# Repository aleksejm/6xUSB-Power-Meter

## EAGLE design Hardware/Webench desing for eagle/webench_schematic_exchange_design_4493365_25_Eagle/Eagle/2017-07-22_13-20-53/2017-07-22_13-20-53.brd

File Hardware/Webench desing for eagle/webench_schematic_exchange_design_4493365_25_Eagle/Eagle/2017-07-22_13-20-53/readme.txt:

**********************************************************
*************  Important Instructions Follow  ************
**********************************************************
 
All files exported to: Z:\\44\\93\\4493365\\25\Eagle\2017-07-22_13-20-53\2017-07-22_13-20-53.xml

**********************************************************
*****************Schematic Instructions  *******************
**********************************************************

To import your new Schematic file into Eagle:

1. Unzip the downloaded folder files to local directory and Start Eagle.
2. Select "File"->"Open"->"Schematic..." from the menu at the top of
the screen.
3. Browse to your newly exported file and select the ".sch" file extension.
4. You should now see your schamtic available in Eagle.

**********************************************************
*******************  PCB Instructions  *******************
**********************************************************

To import your new BOARD file into Eagle:

1. Unzip the downloaded folder files to local directory and Start Eagle.
2. Select "File"->"Open"->"Board..." from the menu at the top of
the screen.
3. Browse to your newly exported file and select the ".brd" file extension.
4. Planes will need to be repoured to update the polygon fills
	1. Once your board is loaded, type "ratsnest" into the command
	   line and press the Enter key.
	2. The polygons should all be filled now.
5. You should now have an image of your board available in Eagle.

**********************************************************
*******************  LIB Instructions  *******************
**********************************************************

To import your new library into Eagle:

1. Start Eagle.
2. Select "File"->"New"->"Library" from the menu.
3. In the blank library window, select "File" -> "Execute Script"
from the menu.
5. Browse to your newly exported Eagle Script file (".scr" file extension)
6. After opening the file, the script will populate the new library.
Layer 93 should NOT exist.
7. Use "File"->Save As: "AcceleratedDesigns_Lib.lbr" and to the desired
location in Eagle native format.
8. Update schematic with the imported library, Select Library and click on Update; open the library file
	and sync. each part.

For additional information, please visit this site:
http://www.accelerated-designs.com/help/Eagle_import.html

You may also find this video helpful:
http://youtu.be/5jGuWY-Yy3Q

**********************************************************
**********************************************************
**********************************************************

Component "C0805C102K5RACTU" renamed to "C0805C102K5RACTU"
Component "EMK212B7474KD-T" renamed to "EMK212B7474KD-T"
Component "08053C104KAT2A" renamed to "08053C104KAT2A"
Component "WB_CURRENT_LOAD" renamed to "WB_CURRENT_LOAD"
Component "6SVPC330M" renamed to "6SVPC330M"
Component "CC0805KRX7R9BB153" renamed to "CC0805KRX7R9BB153"
Component "EMK212B7105KG-T" renamed to "EMK212B7105KG-T"
Component "WB_GND" renamed to "WB_GND"
Component "XAL1010-472MEB" renamed to "XAL1010-472MEB"
Component "CSD16321Q5" renamed to "CSD16321Q5"
Component "CSD18509Q5B" renamed to "CSD18509Q5B"
Component "ERJ-6ENF1002V" renamed to "ERJ-6ENF1002V"
Component "ERJ-6ENF7322V" renamed to "ERJ-6ENF7322V"
Component "CRCW0805464RFKEA" renamed to "CRCW0805464RFKEA"
Component "ERJ-6ENF2373V" renamed to "ERJ-6ENF2373V"
Component "LM3150MH/NOPB" renamed to "LM3150MH/NOPB"
Component "WB_BATTERY" renamed to "WB_BATTERY"
Component "C3216X5R1E476M160AC" renamed to "C3216X5R1E476M160AC"
The Symbol WB_CONTINUATION was missing a RefDes attribute, a refdes was created for the symbol.
The Symbol WB_CONTINUATION was missing a Type attribute, a type was created for the symbol.
The Symbol WB_CONTINUATION was missing a Value attribute, a value was created for the symbol.
The Symbol WB_CFF_BLOCK was missing a RefDes attribute, a refdes was created for the symbol.
The Symbol WB_CFF_BLOCK was missing a Type attribute, a type was created for the symbol.
The Symbol WB_CFF_BLOCK was missing a Value attribute, a value was created for the symbol.
The Symbol WB_BLOCK_IO was missing a RefDes attribute, a refdes was created for the symbol.
The Symbol WB_BLOCK_IO was missing a Type attribute, a type was created for the symbol.
The Symbol WB_BLOCK_IO was missing a Value attribute, a value was created for the symbol.
The Symbol WB_CURRENT_PROBE was missing a RefDes attribute, a refdes was created for the symbol.
The Symbol WB_CURRENT_PROBE was missing a Type attribute, a type was created for the symbol.
The Symbol WB_CURRENT_PROBE was missing a Value attribute, a value was created for the symbol.
The Symbol WB_N_MOSFET was missing a RefDes attribute, a refdes was created for the symbol.
The Symbol WB_N_MOSFET was missing a Type attribute, a type was created for the symbol.
The Symbol WB_N_MOSFET was missing a Value attribute, a value was created for the symbol.
The Symbol WB_LM3150 was missing a RefDes attribute, a refdes was created for the symbol.
The Symbol WB_LM3150 was missing a Type attribute, a type was created for the symbol.
The Symbol WB_LM3150 was missing a Value attribute, a value was created for the symbol.
The Symbol WB_VOLTAGE_PROBE was missing a RefDes attribute, a refdes was created for the symbol.
The Symbol WB_VOLTAGE_PROBE was missing a Type attribute, a type was created for the symbol.
The Symbol WB_VOLTAGE_PROBE was missing a Value attribute, a value was created for the symbol.
The Symbol WB_PWL_VOLTAGE_SOURCE was missing a RefDes attribute, a refdes was created for the symbol.
The Symbol WB_PWL_VOLTAGE_SOURCE was missing a Type attribute, a type was created for the symbol.
The Symbol WB_PWL_VOLTAGE_SOURCE was missing a Value attribute, a value was created for the symbol.
The Symbol WB_SOURCE_RESISTOR was missing a RefDes attribute, a refdes was created for the symbol.
The Symbol WB_SOURCE_RESISTOR was missing a Type attribute, a type was created for the symbol.
The Symbol WB_SOURCE_RESISTOR was missing a Value attribute, a value was created for the symbol.
The Symbol WB_PRIM_PWL_VOLTAGE_SOURCE was missing a RefDes attribute, a refdes was created for the symbol.
The Symbol WB_PRIM_PWL_VOLTAGE_SOURCE was missing a Type attribute, a type was created for the symbol.
The Symbol WB_PRIM_PWL_VOLTAGE_SOURCE was missing a Value attribute, a value was created for the symbol.
The Symbol WB_PRIM_STARTUP_VOLTAGE_SOURCE was missing a RefDes attribute, a refdes was created for the symbol.
The Symbol WB_PRIM_STARTUP_VOLTAGE_SOURCE was missing a Type attribute, a type was created for the symbol.
The Symbol WB_PRIM_STARTUP_VOLTAGE_SOURCE was missing a Value attribute, a value was created for the symbol.
The Symbol WB_STARTUP_VOLTAGE_SOURCE was missing a RefDes attribute, a refdes was created for the symbol.
The Symbol WB_STARTUP_VOLTAGE_SOURCE was missing a Type attribute, a type was created for the symbol.
The Symbol WB_STARTUP_VOLTAGE_SOURCE was missing a Value attribute, a value was created for the symbol.
The Symbol WB_PRIMITIVE_BATTERY was missing a RefDes attribute, a refdes was created for the symbol.
The Symbol WB_PRIMITIVE_BATTERY was missing a Type attribute, a type was created for the symbol.
The Symbol WB_PRIMITIVE_BATTERY was missing a Value attribute, a value was created for the symbol.
The Symbol WB_PWL_CURRENT_LOAD was missing a RefDes attribute, a refdes was created for the symbol.
The Symbol WB_PWL_CURRENT_LOAD was missing a Type attribute, a type was created for the symbol.
The Symbol WB_PWL_CURRENT_LOAD was missing a Value attribute, a value was created for the symbol.
The Symbol WB_LOAD_RESISTOR was missing a RefDes attribute, a refdes was created for the symbol.
The Symbol WB_LOAD_RESISTOR was missing a Type attribute, a type was created for the symbol.
The Symbol WB_LOAD_RESISTOR was missing a Value attribute, a value was created for the symbol.

Ultra Librarian Gold 8.1.204 Process Report

Message - Padstack "RX44Y57D0T" Shape(4) is a CIRCLE with no diameter.
Message - Padstack "RX44Y71D0T" Shape(4) is a CIRCLE with no diameter.
Message - Padstack "RX128Y31D0T" Shape(4) is a CIRCLE with no diameter.
Message - Padstack "RX94Y445D0T" Shape(4) is a CIRCLE with no diameter.
Message - Padstack "RX31p5Y27p56D0T" Shape(4) is a CIRCLE with no diameter.
Message - Padstack "RX4p3Y4p56D0T" Shape(4) is a CIRCLE with no diameter.
Message - Padstack "RX1p37Yp71D0T" Shape(4) is a CIRCLE with no diameter.
Message - Padstack "RX3p85Y4p52D0T" Shape(4) is a CIRCLE with no diameter.
Message - Padstack "RX56Y14D0T" Shape(4) is a CIRCLE with no diameter.
Message - Padstack "RX118Y122D0T" Shape(4) is a CIRCLE with no diameter.
Message - Symbol "WB_CAPACITOR" has as multiple attributes named "TYPE".
One of the attributes was renamed to "TYPE_2".
Message - Component "C0805C102K5RACTU" attribute "Cap" references text style "" that is not in the database.
The default pattern text style "H50s3" was substituted.
Message - Component "C0805C102K5RACTU" attribute "ESR" references text style "" that is not in the database.
The default pattern text style "H50s3" was substituted.
Message - Component "C0805C102K5RACTU" attribute "IRMS" references text style "" that is not in the database.
The default pattern text style "H50s3" was substituted.
Message - Component "C0805C102K5RACTU" attribute "VDC" references text style "" that is not in the database.
The default pattern text style "H50s3" was substituted.
Message - Component "EMK212B7474KD-T" attribute "Cap" references text style "" that is not in the database.
The default pattern text style "H50s3" was substituted.
Message - Component "EMK212B7474KD-T" attribute "ESR" references text style "" that is not in the database.
The default pattern text style "H50s3" was substituted.
Message - Component "EMK212B7474KD-T" attribute "IRMS" references text style "" that is not in the database.
The default pattern text style "H50s3" was substituted.
Message - Component "EMK212B7474KD-T" attribute "VDC" references text style "" that is not in the database.
The default pattern text style "H50s3" was substituted.
Message - Component "08053C104KAT2A" attribute "Cap" references text style "" that is not in the database.
The default pattern text style "H50s3" was substituted.
Message - Component "08053C104KAT2A" attribute "ESR" references text style "" that is not in the database.
The default pattern text style "H50s3" was substituted.
Message - Component "08053C104KAT2A" attribute "IRMS" references text style "" that is not in the database.
The default pattern text style "H50s3" was substituted.
Message - Component "08053C104KAT2A" attribute "VDC" references text style "" that is not in the database.
The default pattern text style "H50s3" was substituted.
Message - Component "6SVPC330M" attribute "Datasheet URL" references text style "" that is not in the database.
The default pattern text style "H50s3" was substituted.
Message - Component "6SVPC330M" attribute "Cap" references text style "" that is not in the database.
The default pattern text style "H50s3" was substituted.
Message - Component "6SVPC330M" attribute "ESR" references text style "" that is not in the database.
The default pattern text style "H50s3" was substituted.
Message - Component "6SVPC330M" attribute "IRMS" references text style "" that is not in the database.
The default pattern text style "H50s3" was substituted.
Message - Component "6SVPC330M" attribute "VDC" references text style "" that is not in the database.
The default pattern text style "H50s3" was substituted.
Message - Component "CC0805KRX7R9BB153" attribute "Cap" references text style "" that is not in the database.
The default pattern text style "H50s3" was substituted.
Message - Component "CC0805KRX7R9BB153" attribute "ESR" references text style "" that is not in the database.
The default pattern text style "H50s3" was substituted.
Message - Component "CC0805KRX7R9BB153" attribute "IRMS" references text style "" that is not in the database.
The default pattern text style "H50s3" was substituted.
Message - Component "CC0805KRX7R9BB153" attribute "VDC" references text style "" that is not in the database.
The default pattern text style "H50s3" was substituted.
Message - Component "EMK212B7105KG-T" attribute "Cap" references text style "" that is not in the database.
The default pattern text style "H50s3" was substituted.
Message - Component "EMK212B7105KG-T" attribute "ESR" references text style "" that is not in the database.
The default pattern text style "H50s3" was substituted.
Message - Component "EMK212B7105KG-T" attribute "IRMS" references text style "" that is not in the database.
The default pattern text style "H50s3" was substituted.
Message - Component "EMK212B7105KG-T" attribute "VDC" references text style "" that is not in the database.
The default pattern text style "H50s3" was substituted.
Message - Component "XAL1010-472MEB" attribute "L" references text style "" that is not in the database.
The default pattern text style "H50s3" was substituted.
Message - Component "XAL1010-472MEB" attribute "DCR" references text style "" that is not in the database.
The default pattern text style "H50s3" was substituted.
Message - Component "XAL1010-472MEB" attribute "IDC" references text style "" that is not in the database.
The default pattern text style "H50s3" was substituted.
Message - Component "ERJ-6ENF1002V" attribute "Resistance" references text style "" that is not in the database.
The default pattern text style "H50s3" was substituted.
Message - Component "ERJ-6ENF1002V" attribute "Power" references text style "" that is not in the database.
The default pattern text style "H50s3" was substituted.
Message - Component "ERJ-6ENF1002V" attribute "Tolerance" references text style "" that is not in the database.
The default pattern text style "H50s3" was substituted.
Message - Component "ERJ-6ENF7322V" attribute "Resistance" references text style "" that is not in the database.
The default pattern text style "H50s3" was substituted.
Message - Component "ERJ-6ENF7322V" attribute "Power" references text style "" that is not in the database.
The default pattern text style "H50s3" was substituted.
Message - Component "ERJ-6ENF7322V" attribute "Tolerance" references text style "" that is not in the database.
The default pattern text style "H50s3" was substituted.
Message - Component "CRCW0805464RFKEA" attribute "Resistance" references text style "" that is not in the database.
The default pattern text style "H50s3" was substituted.
Message - Component "CRCW0805464RFKEA" attribute "Power" references text style "" that is not in the database.
The default pattern text style "H50s3" was substituted.
Message - Component "CRCW0805464RFKEA" attribute "Tolerance" references text style "" that is not in the database.
The default pattern text style "H50s3" was substituted.
Message - Component "ERJ-6ENF2373V" attribute "Resistance" references text style "" that is not in the database.
The default pattern text style "H50s3" was substituted.
Message - Component "ERJ-6ENF2373V" attribute "Power" references text style "" that is not in the database.
The default pattern text style "H50s3" was substituted.
Message - Component "ERJ-6ENF2373V" attribute "Tolerance" references text style "" that is not in the database.
The default pattern text style "H50s3" was substituted.
Message - Component "LM3150MH/NOPB" attribute "Datasheet URL" references text style "" that is not in the database.
The default pattern text style "H50s3" was substituted.
Message - Component "LM3150MH/NOPB" attribute "Frequency" references text style "" that is not in the database.
The default pattern text style "H50s3" was substituted.
Message - Component "LM3150MH/NOPB" attribute "Imax" references text style "" that is not in the database.
The default pattern text style "H50s3" was substituted.
Message - Component "LM3150MH/NOPB" attribute "Package" references text style "" that is not in the database.
The default pattern text style "H50s3" was substituted.
Message - Component "LM3150MH/NOPB" attribute "Mktg_Package" references text style "" that is not in the database.
The default pattern text style "H50s3" was substituted.
Message - Component "LM3150MH/NOPB" attribute "NSID" references text style "" that is not in the database.
The default pattern text style "H50s3" was substituted.

TextStyle count:  24
Padstack count:   10
Pattern count:    7
Symbol count:     25
Component count:  18

Export

Component "C3216X5R1E476M160AC" has the following missing dependency and will be skipped: Footprint "1206L"
Footprint "WB_CURRENT_LOAD" has no layer data mapped and will be skipped.
Component "WB_CURRENT_LOAD" requires footprint "WB_CURRENT_LOAD" and will be skipped.
Footprint "WB_GND" has no layer data mapped and will be skipped.
Component "WB_GND" requires footprint "WB_GND" and will be skipped.
Footprint "WB_BATTERY" has no layer data mapped and will be skipped.
Component "WB_BATTERY" requires footprint "WB_BATTERY" and will be skipped.

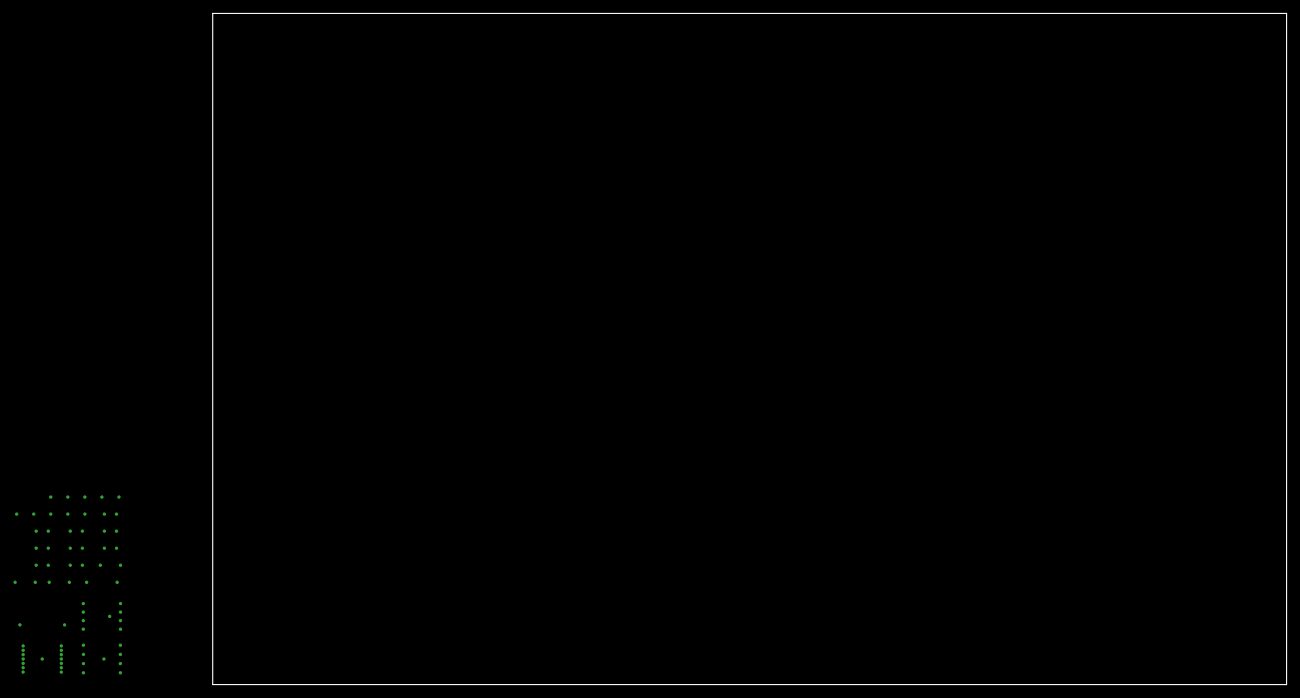
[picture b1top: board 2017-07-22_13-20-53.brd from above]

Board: 2 copper layers, 160.0 x 100.0 mm, 27 parts (0 on the bottom side), 12 nets, no tracks yet.

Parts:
CBST: 470nF; 0805
CBYP: 100nF; 0805
CFF: 1nF; 0805
CIN: 47uF; 1206
CIN_2, CIN_3: 47uF; 1206
COUT: 330uF; SM_RADIAL_6.3AMM
CSS: 15nF; 0805
CVCC: 1uF; 0805
GND1, GND2, GND3, GND4, GND5, GND6, GND7, GND8: WB_GND
IOUT_1: WB_CURRENT_LOAD
L1: 4.7uH; XAL1010
M1: 25V; TRANS_NEXFET_Q5
M2: 40V; TRANS_NEXFET_Q5B
RFB1: 10k; 0805
RFB2: 73.2k; 0805
RILIM: 464; 0805
RON: 237k; 0805
U1: LM3150MH/NOPB; MXA14A
VIN: WB_BATTERY

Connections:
0: CBYP.2, CIN.2, CIN_2.2, CIN_3.2, COUT.2, CSS.2, CVCC.2, GND1.1, GND2.1, GND3.1, GND4.1, GND5.1, GND6.1, GND7.1, GND8.1, IOUT_1.2, M2.1, M2.2, M2.3, RFB1.2, U1.5, U1.9, U1.14, U1.15, VIN.2
1: CSS.1, U1.6
2: CBYP.1, CIN.1, CIN_2.1, CIN_3.1, M1.5, M1.6, M1.7, M1.8, M1.9, RON.1, U1.2, VIN.1
3: RON.2, U1.7
4: CFF.1, COUT.1, IOUT_1.1, L1.2, RFB2.1
5: CFF.2, RFB1.1, RFB2.2, U1.4
6: CBST.2, L1.1, M1.1, M1.2, M1.3, M2.5, M2.6, M2.7, M2.8, M2.9, RILIM.1, U1.10
7: M2.4, U1.13
8: M1.4, U1.11
9: CBST.1, U1.12
10: CVCC.1, U1.1
11: RILIM.2, U1.8

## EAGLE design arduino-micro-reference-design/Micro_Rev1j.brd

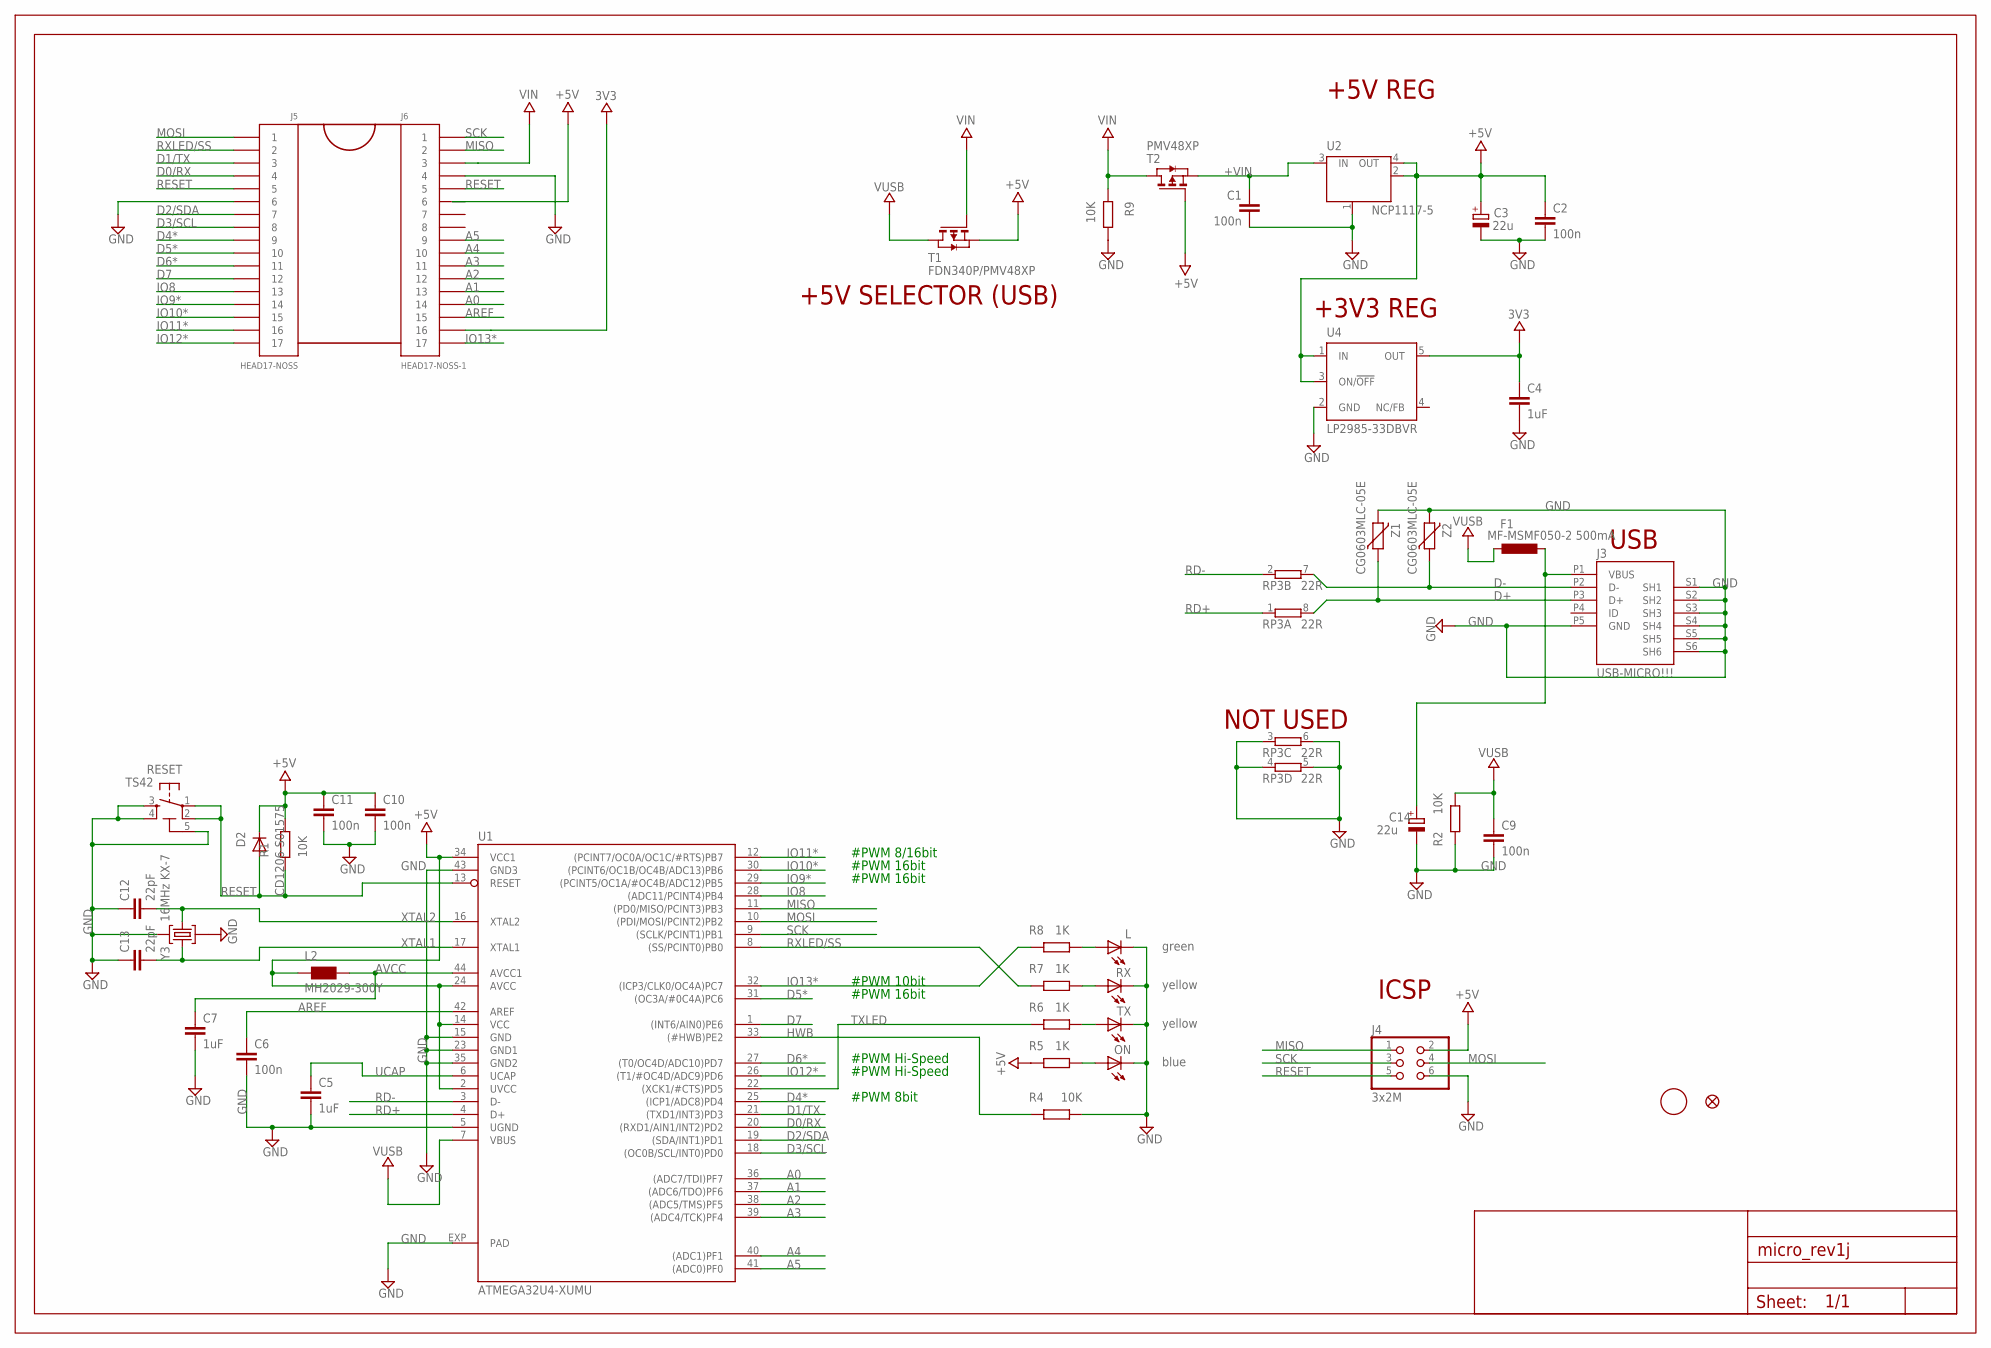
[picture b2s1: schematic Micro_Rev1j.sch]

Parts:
C1, C2, C6, C9, C10, C11: 100n; C0402
C3, C14: 22u; SMC_B
C4, C5, C7: 1uF; C0402
C12, C13: 22pF; C0402
D2: CD1206-S01575; MINIMELF
F1: MF-MSMF050-2 500mA; L1812
FRAME1: DNP; FRAME
J3: USB-MICRO!!!; CON2_USB_MICRO_B_AT
J4: 3x2M; 2X03
J5: HEAD17-NOSS
J6: HEAD17-NOSS-1
L: green; CHIPLED_0805
L2: MH2029-300Y; 0805
ON: blue; CHIPLED_0805
R1, R2, R4, R9: 10K; R0402
R5, R6, R7, R8: 1K; R0402
RESET: TS42
RP3: 22R; CAY16
RX: yellow; CHIPLED_0805
T1: FDN340P/PMV48XP; SOT-23
T2: PMV48XP; SOT-23
TX: yellow; CHIPLED_0805
U1: ATMEGA32U4-XUMU; QFN44ML7X7
U2: NCP1117-5; SOT223
U4: LP2985-33DBVR; SOT23-DBV
U$37: FIDUCIALMOUNT; FIDUCIA-MOUNT
U$53: FIDUCIAL1X2; FIDUCIAL-1X2
Y3: 16MHz KX-7; CRYSTAL-3.2-2.5
Z1, Z2: CG0603MLC-05E; CT/CN0603

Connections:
3V3: C4.1, J6.16, U4.5 (OUT)
+5V: C2.1, C3.+, C10.1, C11.1, D2.C, J4.2, J6.6, L2.1, R1.1, R5.1, T1.2 (S), T2.3 (G), U1.2 (UVCC), U1.14 (VCC), U1.24 (AVCC), U1.34 (VCC1), U2.2 (OUT), U2.4 (OUT), U4.1 (IN), U4.3 (ON/!OFF)
+VIN: C1.1, T2.2 (S), U2.3 (IN)
A0: J6.14, U1.36 ((ADC7/TDI)PF7)
A1: J6.13, U1.37 ((ADC6/TDO)PF6)
A2: J6.12, U1.38 ((ADC5/TMS)PF5)
A3: J6.11, U1.39 ((ADC4/TCK)PF4)
A4: J6.10, U1.40 ((ADC1)PF1)
A5: J6.9, U1.41 ((ADC0)PF0)
AREF: C6.1, J6.15, U1.42 (AREF)
AVCC: C7.1, L2.2, U1.44 (AVCC1)
D0/RX: J5.4, U1.20 ((RXD1/AIN1/INT2)PD2)
D1/TX: J5.3, U1.21 ((TXD1/INT3)PD3)
D2/SDA: J5.7, U1.19 ((SDA/INT1)PD1)
D3/SCL: J5.8, U1.18 ((OC0B/SCL/INT0)PD0)
D4*: J5.9, U1.25 ((ICP1/ADC8)PD4)
D5*: J5.10, U1.31 ((OC3A/#0C4A)PC6)
D6*: J5.11, U1.27 ((T0/OC4D/ADC10)PD7)
D7: J5.12, U1.1 ((INT6/AIN0)PE6)
D+: J3.P3 (D+), RP3.8 (2), Z1.1
D-: J3.P2 (D-), RP3.7 (2), Z2.1
GND: C1.2, C2.2, C3.-, C4.2, C5.2, C6.2, C7.2, C9.2, C10.2, C11.2, C12.1, C13.1, C14.-, J3.P5 (GND), J3.S1 (SH1), J3.S2 (SH2), J3.S3 (SH3), J3.S4 (SH4), J3.S5 (SH5), J3.S6 (SH6), J4.6, J5.6, J6.4, L.C, ON.C, R2.1, R4.2, R9.1, RESET.3, RESET.4, RESET.5 (5-GND), RP3.3 (1), RP3.4 (1), RP3.5 (2), RP3.6 (2), RX.C, TX.C, U1.5 (UGND), U1.15 (GND), U1.23 (GND1), U1.35 (GND2), U1.43 (GND3), U1.EXP (PAD), U2.1 (GND/ADJ), U4.2 (GND), Y3.2 (GND), Y3.4 (GND), Z1.2, Z2.2
HWB: R4.1, U1.33 ((#HWB)PE2)
IO8: J5.13, U1.28 ((ADC11/PCINT4)PB4)
IO9*: J5.14, U1.29 ((PCINT5/OC1A/#OC4B/ADC12)PB5)
IO10*: J5.15, U1.30 ((PCINT6/OC1B/OC4B/ADC13)PB6)
IO11*: J5.16, U1.12 ((PCINT7/OC0A/OC1C/#RTS)PB7)
IO12*: J5.17, U1.26 ((T1/#OC4D/ADC9)PD6)
IO13*: J6.17, R8.1, U1.32 ((ICP3/CLK0/OC4A)PC7)
MISO: J4.1, J6.2, U1.11 ((PD0/MISO/PCINT3)PB3)
MOSI: J4.4, J5.1, U1.10 ((PDI/MOSI/PCINT2)PB2)
unnamed: R7.2, RX.A
unnamed: ON.A, R5.2
unnamed: R6.2, TX.A
unnamed: L.A, R8.2
RD+: RP3.1, U1.4 (D+)
RD-: RP3.2 (1), U1.3 (D-)
RESET: D2.A, J4.5, J5.5, J6.5, R1.2, RESET.1, RESET.2, U1.13 (RESET)
RXLED/SS: J5.2, R7.1, U1.8 ((SS/PCINT0)PB0)
SCK: J4.3, J6.1, U1.9 ((SCLK/PCINT1)PB1)
TXLED: R6.1, U1.22 ((XCK1/#CTS)PD5)
UCAP: C5.1, U1.6 (UCAP)
VIN: J6.3, R9.2, T1.3 (G), T2.1 (D)
VUSB: C9.1, F1.2, R2.2, T1.1 (D), U1.7 (VBUS)
VUSBD: C14.+, F1.1, J3.P1 (VBUS)
XTAL1: C13.2, U1.17 (XTAL1), Y3.3 (C2)
XTAL2: C12.2, U1.16 (XTAL2), Y3.1 (C1)

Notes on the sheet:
+5V REG
ICSP
USB
+5V SELECTOR (USB)
NOT USED
+3V3 REG
#PWM 8bit
#PWM Hi-Speed
#PWM 16bit
#PWM 10bit
#PWM 8/16bit

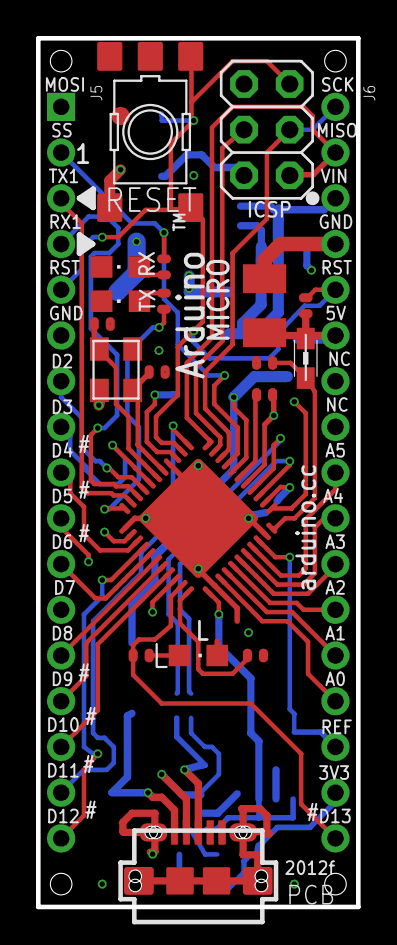
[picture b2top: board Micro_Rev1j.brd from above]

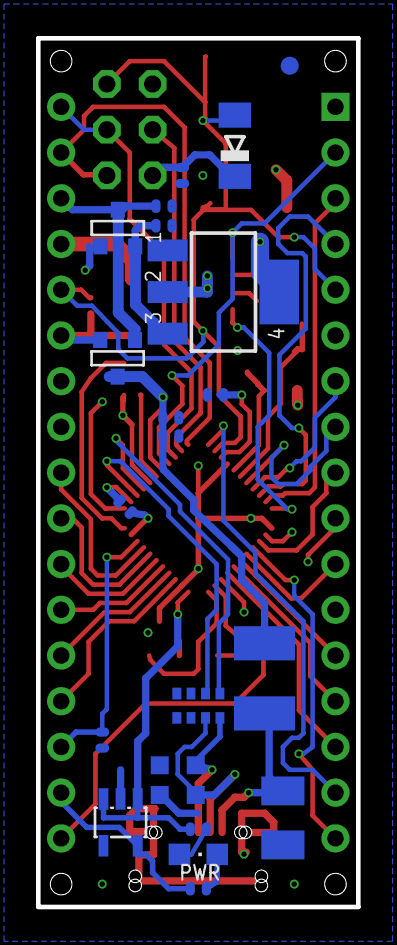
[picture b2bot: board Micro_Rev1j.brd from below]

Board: 4 copper layers, 17.8 x 48.3 mm, 45 parts (22 on the bottom side), 47 nets.

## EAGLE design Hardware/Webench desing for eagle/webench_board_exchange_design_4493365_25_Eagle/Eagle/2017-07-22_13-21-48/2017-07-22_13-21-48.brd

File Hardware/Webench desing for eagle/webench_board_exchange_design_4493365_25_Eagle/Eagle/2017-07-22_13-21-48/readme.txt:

**********************************************************
*************  Important Instructions Follow  ************
**********************************************************
 
All files exported to: Z:\\44\\93\\4493365\\25\Eagle\2017-07-22_13-21-48\2017-07-22_13-21-48.xml

**********************************************************
*****************Schematic Instructions  *******************
**********************************************************

To import your new Schematic file into Eagle:

1. Unzip the downloaded folder files to local directory and Start Eagle.
2. Select "File"->"Open"->"Schematic..." from the menu at the top of
the screen.
3. Browse to your newly exported file and select the ".sch" file extension.
4. You should now see your schamtic available in Eagle.

**********************************************************
*******************  PCB Instructions  *******************
**********************************************************

To import your new BOARD file into Eagle:

1. Unzip the downloaded folder files to local directory and Start Eagle.
2. Select "File"->"Open"->"Board..." from the menu at the top of
the screen.
3. Browse to your newly exported file and select the ".brd" file extension.
4. Planes will need to be repoured to update the polygon fills
	1. Once your board is loaded, type "ratsnest" into the command
	   line and press the Enter key.
	2. The polygons should all be filled now.
5. You should now have an image of your board available in Eagle.

**********************************************************
*******************  LIB Instructions  *******************
**********************************************************

To import your new library into Eagle:

1. Start Eagle.
2. Select "File"->"New"->"Library" from the menu.
3. In the blank library window, select "File" -> "Execute Script"
from the menu.
5. Browse to your newly exported Eagle Script file (".scr" file extension)
6. After opening the file, the script will populate the new library.
Layer 93 should NOT exist.
7. Use "File"->Save As: "AcceleratedDesigns_Lib.lbr" and to the desired
location in Eagle native format.
8. Update schematic with the imported library, Select Library and click on Update; open the library file
	and sync. each part.

For additional information, please visit this site:
http://www.accelerated-designs.com/help/Eagle_import.html

You may also find this video helpful:
http://youtu.be/5jGuWY-Yy3Q

**********************************************************
**********************************************************
**********************************************************

Component "6SVPC330M" renamed to "6SVPC330M"
Component "EMK212B7474KD-T" renamed to "EMK212B7474KD-T"
Component "08053C104KAT2A" renamed to "08053C104KAT2A"
Component "C0805C102K5RACTU" renamed to "C0805C102K5RACTU"
Component "C3216X5R1E476M160AC" renamed to "C3216X5R1E476M160AC"
Component "ERJ-6ENF7322V" renamed to "ERJ-6ENF7322V"
Component "CC0805KRX7R9BB153" renamed to "CC0805KRX7R9BB153"
Component "EMK212B7105KG-T" renamed to "EMK212B7105KG-T"
Component "B350A-13-F" renamed to "B350A-13-F"
Component "LM3150MH/NOPB" renamed to "LM3150MH/NOPB"
Component "XAL1010-472MEB" renamed to "XAL1010-472MEB"
Component "ERJ-6ENF1002V" renamed to "ERJ-6ENF1002V"
Component "ERJ-6ENF2373V" renamed to "ERJ-6ENF2373V"
Component "C0805C223K5RACTU" renamed to "C0805C223K5RACTU"
Component "TP-1502" renamed to "TP-1502"
Component "CSD16321Q5" renamed to "CSD16321Q5"
Component "CSD18509Q5B" renamed to "CSD18509Q5B"

Ultra Librarian Gold 8.1.204 Process Report

Message - Padstack "RX44Y57D0T" Shape(4) is a CIRCLE with no diameter.
Message - Padstack "RX44Y71D0T" Shape(4) is a CIRCLE with no diameter.
Message - Padstack "RX128Y31D0T" Shape(4) is a CIRCLE with no diameter.
Message - Padstack "RX86Y64D0T" Shape(4) is a CIRCLE with no diameter.
Message - Padstack "RX94Y445D0T" Shape(4) is a CIRCLE with no diameter.
Message - Padstack "RX56Y14D0T" Shape(4) is a CIRCLE with no diameter.
Message - Padstack "RX118Y122D0T" Shape(4) is a CIRCLE with no diameter.
Message - Padstack "RX31p5Y27p56D0T" Shape(4) is a CIRCLE with no diameter.
Message - Padstack "RX4p3Y4p56D0T" Shape(4) is a CIRCLE with no diameter.
Message - Padstack "RX1p37Yp71D0T" Shape(4) is a CIRCLE with no diameter.
Message - Padstack "RX3p85Y4p52D0T" Shape(4) is a CIRCLE with no diameter.
Message - Component "6SVPC330M" attribute "Datasheet URL" references text style "" that is not in the database.
The default pattern text style "H50s3" was substituted.
Message - Component "6SVPC330M" attribute "Cap" references text style "" that is not in the database.
The default pattern text style "H50s3" was substituted.
Message - Component "6SVPC330M" attribute "ESR" references text style "" that is not in the database.
The default pattern text style "H50s3" was substituted.
Message - Component "6SVPC330M" attribute "IRMS" references text style "" that is not in the database.
The default pattern text style "H50s3" was substituted.
Message - Component "6SVPC330M" attribute "VDC" references text style "" that is not in the database.
The default pattern text style "H50s3" was substituted.
Message - Component "EMK212B7474KD-T" attribute "Cap" references text style "" that is not in the database.
The default pattern text style "H50s3" was substituted.
Message - Component "EMK212B7474KD-T" attribute "ESR" references text style "" that is not in the database.
The default pattern text style "H50s3" was substituted.
Message - Component "EMK212B7474KD-T" attribute "IRMS" references text style "" that is not in the database.
The default pattern text style "H50s3" was substituted.
Message - Component "EMK212B7474KD-T" attribute "VDC" references text style "" that is not in the database.
The default pattern text style "H50s3" was substituted.
Message - Component "08053C104KAT2A" attribute "Cap" references text style "" that is not in the database.
The default pattern text style "H50s3" was substituted.
Message - Component "08053C104KAT2A" attribute "ESR" references text style "" that is not in the database.
The default pattern text style "H50s3" was substituted.
Message - Component "08053C104KAT2A" attribute "IRMS" references text style "" that is not in the database.
The default pattern text style "H50s3" was substituted.
Message - Component "08053C104KAT2A" attribute "VDC" references text style "" that is not in the database.
The default pattern text style "H50s3" was substituted.
Message - Component "C0805C102K5RACTU" attribute "Cap" references text style "" that is not in the database.
The default pattern text style "H50s3" was substituted.
Message - Component "C0805C102K5RACTU" attribute "ESR" references text style "" that is not in the database.
The default pattern text style "H50s3" was substituted.
Message - Component "C0805C102K5RACTU" attribute "IRMS" references text style "" that is not in the database.
The default pattern text style "H50s3" was substituted.
Message - Component "C0805C102K5RACTU" attribute "VDC" references text style "" that is not in the database.
The default pattern text style "H50s3" was substituted.
Message - Component "ERJ-6ENF7322V" attribute "Resistance" references text style "" that is not in the database.
The default pattern text style "H50s3" was substituted.
Message - Component "ERJ-6ENF7322V" attribute "Power" references text style "" that is not in the database.
The default pattern text style "H50s3" was substituted.
Message - Component "ERJ-6ENF7322V" attribute "Tolerance" references text style "" that is not in the database.
The default pattern text style "H50s3" was substituted.
Message - Component "CC0805KRX7R9BB153" attribute "Cap" references text style "" that is not in the database.
The default pattern text style "H50s3" was substituted.
Message - Component "CC0805KRX7R9BB153" attribute "ESR" references text style "" that is not in the database.
The default pattern text style "H50s3" was substituted.
Message - Component "CC0805KRX7R9BB153" attribute "IRMS" references text style "" that is not in the database.
The default pattern text style "H50s3" was substituted.
Message - Component "CC0805KRX7R9BB153" attribute "VDC" references text style "" that is not in the database.
The default pattern text style "H50s3" was substituted.
Message - Component "EMK212B7105KG-T" attribute "Cap" references text style "" that is not in the database.
The default pattern text style "H50s3" was substituted.
Message - Component "EMK212B7105KG-T" attribute "ESR" references text style "" that is not in the database.
The default pattern text style "H50s3" was substituted.
Message - Component "EMK212B7105KG-T" attribute "IRMS" references text style "" that is not in the database.
The default pattern text style "H50s3" was substituted.
Message - Component "EMK212B7105KG-T" attribute "VDC" references text style "" that is not in the database.
The default pattern text style "H50s3" was substituted.
Message - Component "B350A-13-F" attribute "Datasheet URL" references text style "" that is not in the database.
The default pattern text style "H50s3" was substituted.
Message - Component "B350A-13-F" attribute "Io" references text style "" that is not in the database.
The default pattern text style "H50s3" was substituted.
Message - Component "B350A-13-F" attribute "VRRM" references text style "" that is not in the database.
The default pattern text style "H50s3" was substituted.
Message - Component "B350A-13-F" attribute "VFatIo" references text style "" that is not in the database.
The default pattern text style "H50s3" was substituted.
Message - Component "LM3150MH/NOPB" attribute "Datasheet URL" references text style "" that is not in the database.
The default pattern text style "H50s3" was substituted.
Message - Component "LM3150MH/NOPB" attribute "Frequency" references text style "" that is not in the database.
The default pattern text style "H50s3" was substituted.
Message - Component "LM3150MH/NOPB" attribute "Imax" references text style "" that is not in the database.
The default pattern text style "H50s3" was substituted.
Message - Component "LM3150MH/NOPB" attribute "Package" references text style "" that is not in the database.
The default pattern text style "H50s3" was substituted.
Message - Component "LM3150MH/NOPB" attribute "Mktg_Package" references text style "" that is not in the database.
The default pattern text style "H50s3" was substituted.
Message - Component "LM3150MH/NOPB" attribute "NSID" references text style "" that is not in the database.
The default pattern text style "H50s3" was substituted.
Message - Component "XAL1010-472MEB" attribute "L" references text style "" that is not in the database.
The default pattern text style "H50s3" was substituted.
Message - Component "XAL1010-472MEB" attribute "DCR" references text style "" that is not in the database.
The default pattern text style "H50s3" was substituted.
Message - Component "XAL1010-472MEB" attribute "IDC" references text style "" that is not in the database.
The default pattern text style "H50s3" was substituted.
Message - Component "ERJ-6ENF1002V" attribute "Resistance" references text style "" that is not in the database.
The default pattern text style "H50s3" was substituted.
Message - Component "ERJ-6ENF1002V" attribute "Power" references text style "" that is not in the database.
The default pattern text style "H50s3" was substituted.
Message - Component "ERJ-6ENF1002V" attribute "Tolerance" references text style "" that is not in the database.
The default pattern text style "H50s3" was substituted.
Message - Component "ERJ-6ENF2373V" attribute "Resistance" references text style "" that is not in the database.
The default pattern text style "H50s3" was substituted.
Message - Component "ERJ-6ENF2373V" attribute "Power" references text style "" that is not in the database.
The default pattern text style "H50s3" was substituted.
Message - Component "ERJ-6ENF2373V" attribute "Tolerance" references text style "" that is not in the database.
The default pattern text style "H50s3" was substituted.
Message - Component "C0805C223K5RACTU" attribute "Cap" references text style "" that is not in the database.
The default pattern text style "H50s3" was substituted.
Message - Component "C0805C223K5RACTU" attribute "ESR" references text style "" that is not in the database.
The default pattern text style "H50s3" was substituted.
Message - Component "C0805C223K5RACTU" attribute "IRMS" references text style "" that is not in the database.
The default pattern text style "H50s3" was substituted.
Message - Component "C0805C223K5RACTU" attribute "VDC" references text style "" that is not in the database.
The default pattern text style "H50s3" was substituted.

TextStyle count:  24
Padstack count:   16
Pattern count:    9
Symbol count:     9
Component count:  17

Export

Component "C3216X5R1E476M160AC" has the following missing dependency and will be skipped: Footprint "1206L"

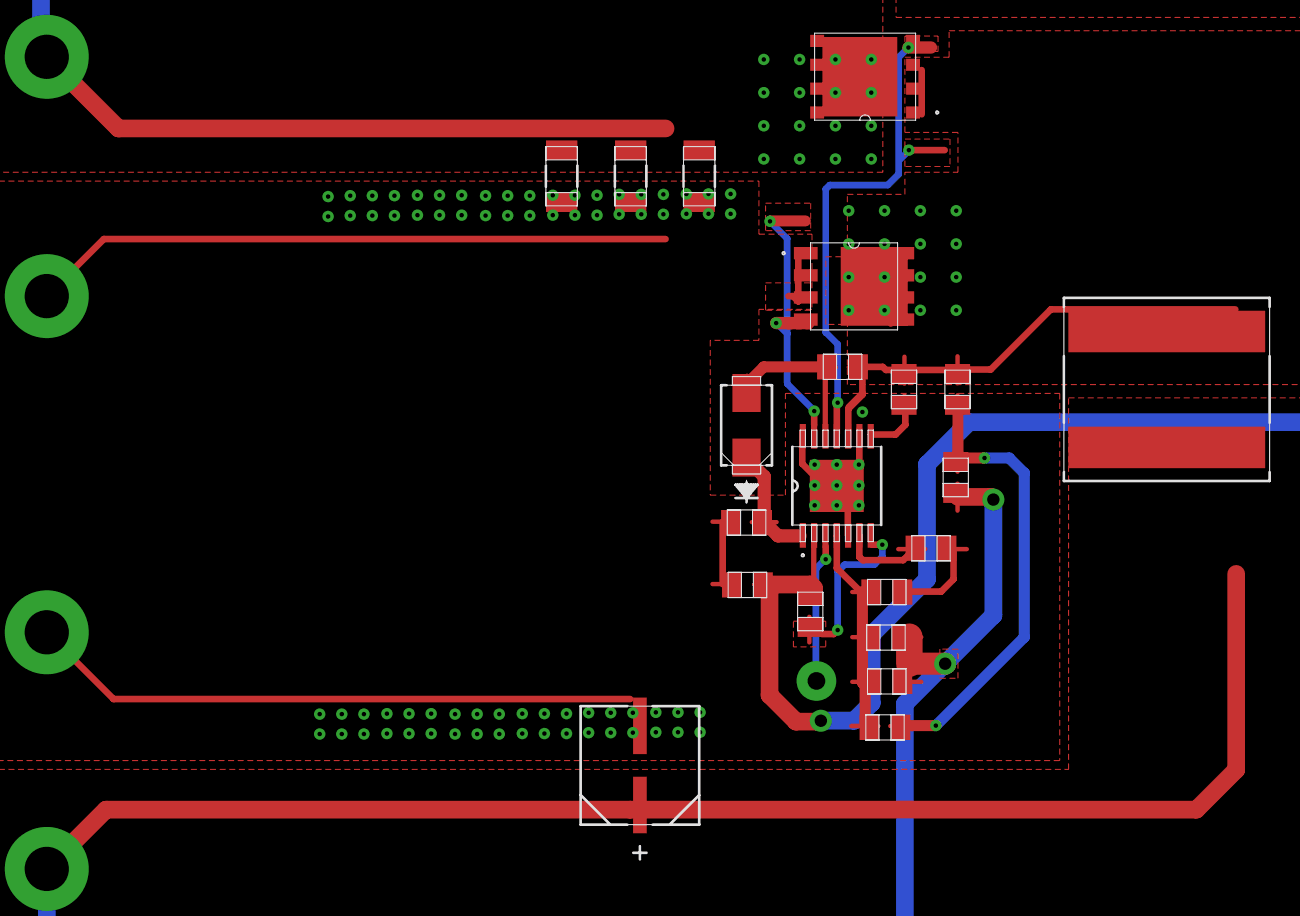
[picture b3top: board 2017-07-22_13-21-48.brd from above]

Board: 4 copper layers, 26 parts (0 on the bottom side), 14 nets.

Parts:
CAC: 0805
CBST: 0805
CBYP: 0805
CFF: 0805
CIN_1, CIN_2, CIN_3: 1206
COUT: SM_RADIAL_6.3AMM
CR: 0805
CSS: 0805
CVCC: 0805
DBST: SMA
EN: TP-1502
GND, GND1: TP-1502
L1: XAL1010
M1: TRANS_NEXFET_Q5
M2: TRANS_NEXFET_Q5B
RFB1, RFB2: 0805
RLIM: 0805
RON: 0805
RR: 0805
U1: MXA14A
VIN: TP-1502
VOUT: TP-1502

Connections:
0: CBYP.2, CIN_1.2, CIN_2.2, CIN_3.2, COUT.2, CSS.2, CVCC.2, GND.1, GND1.1, M2.1, M2.2, M2.3, RFB1.2, U1.5, U1.9, U1.14, U1.15
1: CSS.1, U1.6
2: CBYP.1, CIN_1.1, CIN_2.1, CIN_3.1, M1.5, M1.6, M1.7, M1.8, M1.9, RON.1, U1.2, VIN.1
3: RON.2, U1.7
4: CFF.1, COUT.1, CR.2, L1.2, RFB2.1, VOUT.1
5: CAC.1, CFF.2, RFB1.1, RFB2.2, U1.4
6: CBST.2, L1.1, M1.1, M1.2, M1.3, M2.5, M2.6, M2.7, M2.8, M2.9, RLIM.1, RR.2, U1.10
7: M2.4, U1.13
8: M1.4, U1.11
9: CBST.1, DBST.2, U1.12
10: CVCC.1, DBST.1, U1.1
11: RLIM.2, U1.8
18: EN.1, U1.3
25: CAC.2, CR.1, RR.1

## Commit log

2016-04-18 :boom::camel: Added .gitattributes & .gitignore files
2016-04-18 Revert ":boom::camel: Added .gitattributes & .gitignore files"
    This reverts commit ec87cd9a793b3f8b229a42348b66e58fb7790340.
2016-04-20 6 port USB power meter with OLED display
    6 port USB power meter/PSU with OLED display
2016-05-06 Schematic updates
2016-05-16 Removed some files
2016-05-26 Updated pcb
    Updated schematic and solved some pcb mistakes
2016-05-31 Upd_sch
    Updated schematic and PCB
2016-06-01 Updates schematic
    Updated schematic and added datasheets
2016-06-07 Upd
    Schematic updates and PCB

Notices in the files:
parts and their libraries:
Arduino-utility: Copyright (c) 2016-2017 Arduino LLC.  All right reserved.
